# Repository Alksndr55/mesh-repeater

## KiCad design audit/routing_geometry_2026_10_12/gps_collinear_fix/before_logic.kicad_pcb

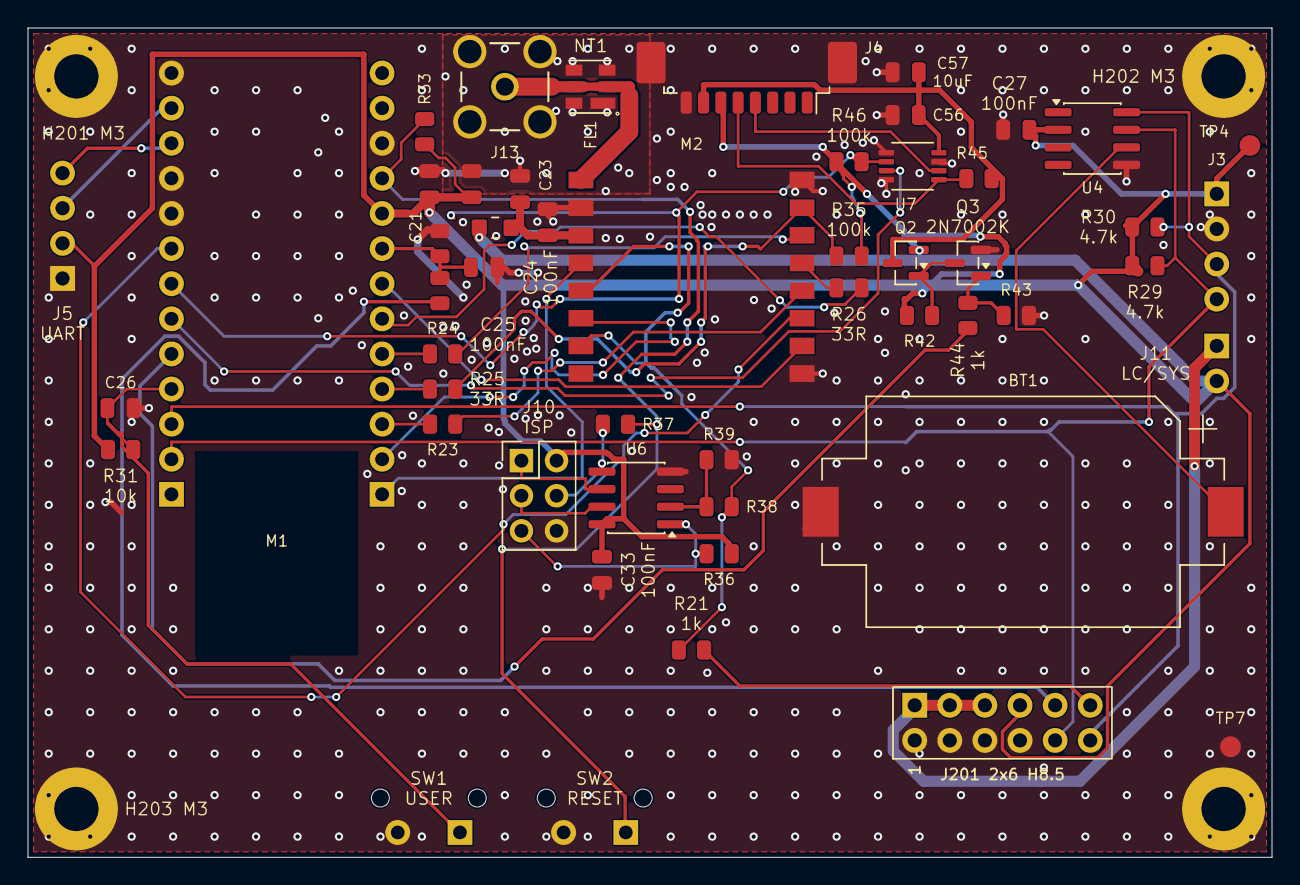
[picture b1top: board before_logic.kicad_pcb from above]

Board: 2 copper layers, 90.0 x 60.0 mm, 57 parts (0 on the bottom side), 42 nets.

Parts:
BT1: CR2032 / holder; BatteryHolder_Keystone_1060_1x2032__V2_BT1
C21: 10uF 16V X7R; C_0805_2012Metric__V2_C21
C22: 100nF 50V X7R; C_0805_2012Metric__V2_C22
C23: 22uF 25V X5R; C_0805_2012Metric__V2_C23
C24: 100nF 50V X7R; C_0805_2012Metric__V2_C24
C25: 100nF 50V X7R; C_0805_2012Metric__V2_C25
C26: 100nF 50V X7R; C_0805_2012Metric__V2_C26
C27: 100nF 50V X7R; C_0805_2012Metric__V2_C27
C33: 100nF 50V X7R; C_0805_2012Metric__V2_C33
C56: 100nF 50V X7R; C_0805_2012Metric__V2_C56
C57: 10uF 16V X7R; C_0805_2012Metric__V2_C57
FB1: 60R@100MHz / 3A; Ferrite_Murata_BLM21PG__V2_FB1
FL1: S869M000S003; SAW_AEL_DCC6C_S869M000S003__V2_FL1
H201: M3 GND contact; GND_M3_D3.2_OD6__V2_H201
H202: M3 GND contact; GND_M3_D3.2_OD6__V2_H202
H203: M3 GND contact; GND_M3_D3.2_OD6__V2_H203
H204: M3 GND contact; GND_M3_D3.2_OD6__V2_H204
J3: I2C3V3; Connfly_DS1022_1x04RUF11_B_Horizontal__V2_J3
J4: GPS / T114 P3; Molex_PicoBlade_53261-0871_1x08-1MP_P1.25mm_Horizontal__V2_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
J5: UART3V3; Connfly_DS1022_1x04RUF11_B_Horizontal__V2_J5
J10: AVR ISP 3V3; PinHeader_2x03_P2.54mm_Vertical__V2_J10
J11: LC OUT - SYS 3V3; Connfly_DS1022_1x02RUF11_B_Horizontal__V2_J11
J13: SMA 50Ohm; SMA_KLS1_SMA002_B_Horizontal__V2_J13
J201: INTERBOARD 2x6 VERTICAL; Ali_PinSocket_2x06_P2.54_H8.5_v2_mirror__V2_J201
M1: NiceNano_CLONE_MODIFIED; NiceNano_13x2_Socket__V2_M1
M2: HT-RA62; HT_RA62__V2_M2
NT1: Cu link / cut for FL1; RF_Cut_Link_0p6__V2_NT1
Q2: AO3401A; SOT-23__V2_Q2
Q3: 2N7002K; SOT-23__V2_Q3
R21: 1k; R_0805_2012Metric__V2_R21
R23: 33R; R_0805_2012Metric__V2_R23
R24: 33R; R_0805_2012Metric__V2_R24
R25: 33R; R_0805_2012Metric__V2_R25
R26: 33R; R_0805_2012Metric__V2_R26
R27: 2.2M 0.1%; R_0805_2012Metric__V2_R27
R28: 2.2M 0.1%; R_0805_2012Metric__V2_R28
R29: 4.7k; R_0805_2012Metric__V2_R29
R30: 4.7k; R_0805_2012Metric__V2_R30
R31: 10k; R_0805_2012Metric__V2_R31
R33: 10k; R_0805_2012Metric__V2_R33
R35: 100k; R_0805_2012Metric__V2_R35
R36: 10k; R_0805_2012Metric__V2_R36
R37: 0R; R_0805_2012Metric__V2_R37
R38: 1k; R_0805_2012Metric__V2_R38
R39: 100k; R_0805_2012Metric__V2_R39
R42: 100k; R_0805_2012Metric__V2_R42
R43: 100k; R_0805_2012Metric__V2_R43
R44: 1k; R_0805_2012Metric__V2_R44
R45: 100k; R_0805_2012Metric__V2_R45
R46: 100k; R_0805_2012Metric__V2_R46
SW1: USER; SW_TE_1825027_2_Side__V2_SW1
SW2: RESET; SW_TE_1825027_2_Side__V2_SW2
TP4: SYS_3V3; TestPoint_Pad_D1.5mm__V2_TP4
TP7: GND; TestPoint_Pad_D1.5mm__V2_TP7
U4: DS3231MZ+TRL; SOIC-8_3.9x4.9mm_P1.27mm__V2_U4
U6: ATtiny13A-SSU; SOIC-8_3.9x4.9mm_P1.27mm__V2_U6
U7: SN74LVC2G125; TI_DCT0008A__V2_U7

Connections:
/2. RTC_IO/GPS_EN_GATE: Q3.1 (G), R43.1, R44.2
/2. RTC_IO/GPS_GATE: Q2.1 (G), Q3.3 (D), R42.2
/2. RTC_IO/RTC_BAT: BT1.1 (+), U4.6 (VBAT)
/ANT_RF: FL1.2 (IN), M2.1 (ANT), NT1.1 (A)
/ANT_SMA: FL1.5 (OUT), J13.1 (SIGNAL), NT1.2 (B)
/RADIO_3V3: C23.1, C24.1, FB1.2, M2.3 (3V3_3)
/RADIO_BUSY: M1.7 (P0.29_/_BUSY), M2.10 (BUSY_10)
/RADIO_DIO1: M1.2 (P0.10_/_DIO1), M2.6 (DIO1_6)
/RADIO_RST: M1.1 (P0.09_/_RADIO_RST), M2.4 (RST_4)
/RADIO_RXEN: M1.21 (P0.17_/_RXEN), M2.11 (RXEN_11)
BAT: J201.9, R27.1
BAT_ADC: C25.1, M1.8 (P0.31_/_BAT_ADC), R27.2, R28.1
FILTER_OUT: J11.1, J201.1, J201.3, J201.5
GND: BT1.2 (-), C21.2, C22.2, C23.2, C24.2, C25.2, C26.2, C27.2, C33.2, C56.2, C57.2, FL1.1 (GND), FL1.3 (GND), FL1.4 (GND), FL1.6 (GND), H201.1, H202.1, H203.1, H204.1, J3.2, J4.8 (GND), J4.MP, J5.1, J10.6, J13.2 (GND), J201.2, J201.4, J201.6, J201.8, M1.11 (GND), M1.22 (GND), M1.23 (GND), M1.26 (GND), M2.2 (GND_2), M2.9 (GND_9), M2.16 (GND_16), Q3.2 (S), R28.2, R39.2, R43.2, SW1.2, SW2.2, TP7.1, U4.5 (GND), U6.4 (GND), U7.1 (~OE1), U7.4 (GND), U7.7 (~OE2)
GPS_3V3: C56.1, C57.1, J4.7 (VCC), Q2.3 (D), R45.1, U7.8 (VCC_GPS)
GPS_EN: M1.18 (P0.24_/_GPS_EN_/_DIGITAL_OUT), R44.1
GPS_RX_EXT: J4.4 (RXD_GPS), U7.6 (1Y_/_GPS_RX)
GPS_RX_MCU: M1.19 (P0.22_/_GPS_RX), U7.3 (2Y_/_MCU_RX)
GPS_TX_EXT: J4.5 (TXD_GPS), R45.2, U7.5 (2A_/_GPS_TX)
GPS_TX_MCU: M1.20 (P0.20_/_GPS_TX), R46.2, U7.2 (1A_/_MCU_TX)
MCU_RESET: M1.10 (RESET), R33.2, R37.2, SW2.1
MODE: J201.11, R21.2
unnamed: M1.6 (P0.02_/_MISO), R26.2
unnamed: M1.3 (P1.11_/_SCK), R23.1
unnamed: M1.4 (P1.13_/_NSS), R25.1
unnamed: M1.5 (P1.15_/_MOSI), R24.1
unnamed: M2.13 (MISO_13), R26.1
unnamed: M2.14 (MOSI_14), R24.2
unnamed: M2.15 (NSS_15), R25.2, R35.2
unnamed: M2.12 (SCK_12), R23.2
unnamed: R38.2, R39.1, U6.2 (PB3_/_TXEN_IN)
RADIO_TXEN: M2.5 (TXEN_=_DIO2_5), M2.7 (DIO2_=_TXEN_7), R21.1, R38.1
SCL: J3.3, J201.12, M1.16 (P0.11_/_SCL), R30.2, U4.8 (SCL)
SDA: J3.4, J201.10, M1.15 (P1.04_/_SDA), R29.2, U4.7 (SDA)
SYS_3V3: C21.1, C22.1, C27.1, C33.1, FB1.1, J3.1, J4.6 (V_BCKP), J5.2, J10.2, J11.2, J201.7, M1.9 (VCC_/_MOD_3V3), Q2.2 (S), R29.1, R30.1, R31.1, R33.1, R35.1, R36.1, R42.1, R46.1, TP4.1, U4.2 (VCC), U6.8 (VCC)
UART_RX: J5.4, M1.24 (P0.08_/_UART_RX)
UART_TX: J5.3, M1.25 (P0.06_/_UART_TX)
USER_BTN: C26.1, M1.17 (P1.00_/_USER_BTN), R31.2, SW1.1
WDT_MISO: J10.1, U6.6 (PB1_/_MISO)
WDT_MOSI_RESET: J10.4, R37.1, U6.5 (PB0_/_RESET_OD_/_MOSI)
WDT_RESET: J10.5, R36.2, U6.1 (PB5_/_RESET)
WDT_SCK: J10.3, U6.7 (PB2_/_SCK)
